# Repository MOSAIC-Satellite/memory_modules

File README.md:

# memory_modules
Repository for all expandable memory modules compatable with MOSAIC and a template for making more.

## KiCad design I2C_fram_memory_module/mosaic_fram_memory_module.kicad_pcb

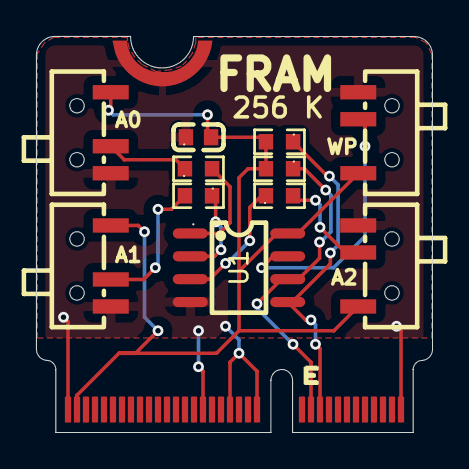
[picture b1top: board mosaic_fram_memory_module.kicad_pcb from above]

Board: 2 copper layers, 22.0 x 22.0 mm, 12 parts (0 on the bottom side), 11 nets.

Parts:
C1: 10 uF; C0603
J1: M.2-CARD-E-22_MEMORY_STANDARD
R1, R2, R3, R4, R5: 10 kOhm; R0603
U1: MB85RC256VPNF-G-JNERE1; MB85RC256_FRAM
U2, U3, U4, U5: MS-1290N; SMD_slide_switch

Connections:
+3.3V: C1.2, J1.73 (3.3V), R1.2, R2.2, U1.8 (VDD), U2.1, U3.1, U4.1, U5.1
/A0_Switch: R3.1, U2.2
/A1_Switch: R4.2, U3.2
/A2_Switch: R5.2, U4.2
/SCL: J1.21 (I2C_SCL), R1.1, U1.6 (SCL)
/SDA: J1.19 (I2C_SDA), R2.1, U1.5 (SDA)
/WP_Switch: U1.7 (WP), U5.2
GND: C1.1, J1.1 (GND), J1.33 (GND), J1.39 (GND), J1.45 (GND), J1.75 (GND), U1.4 (VSS), U2.3, U3.3, U4.3, U5.3
unnamed: R3.2, U1.1 (A0)
unnamed: R4.1, U1.2 (A1)
unnamed: R5.1, U1.3 (A2)

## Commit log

2025-07-24 initial file upload
2025-07-24 finished fram_mem module
2025-07-24 added production folder
2026-01-04 Added new modules

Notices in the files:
I2C_fram_memory_module/mosaic_fram_memory_module.kicad_pcb:
Copyright (c) 2022 - 2025
